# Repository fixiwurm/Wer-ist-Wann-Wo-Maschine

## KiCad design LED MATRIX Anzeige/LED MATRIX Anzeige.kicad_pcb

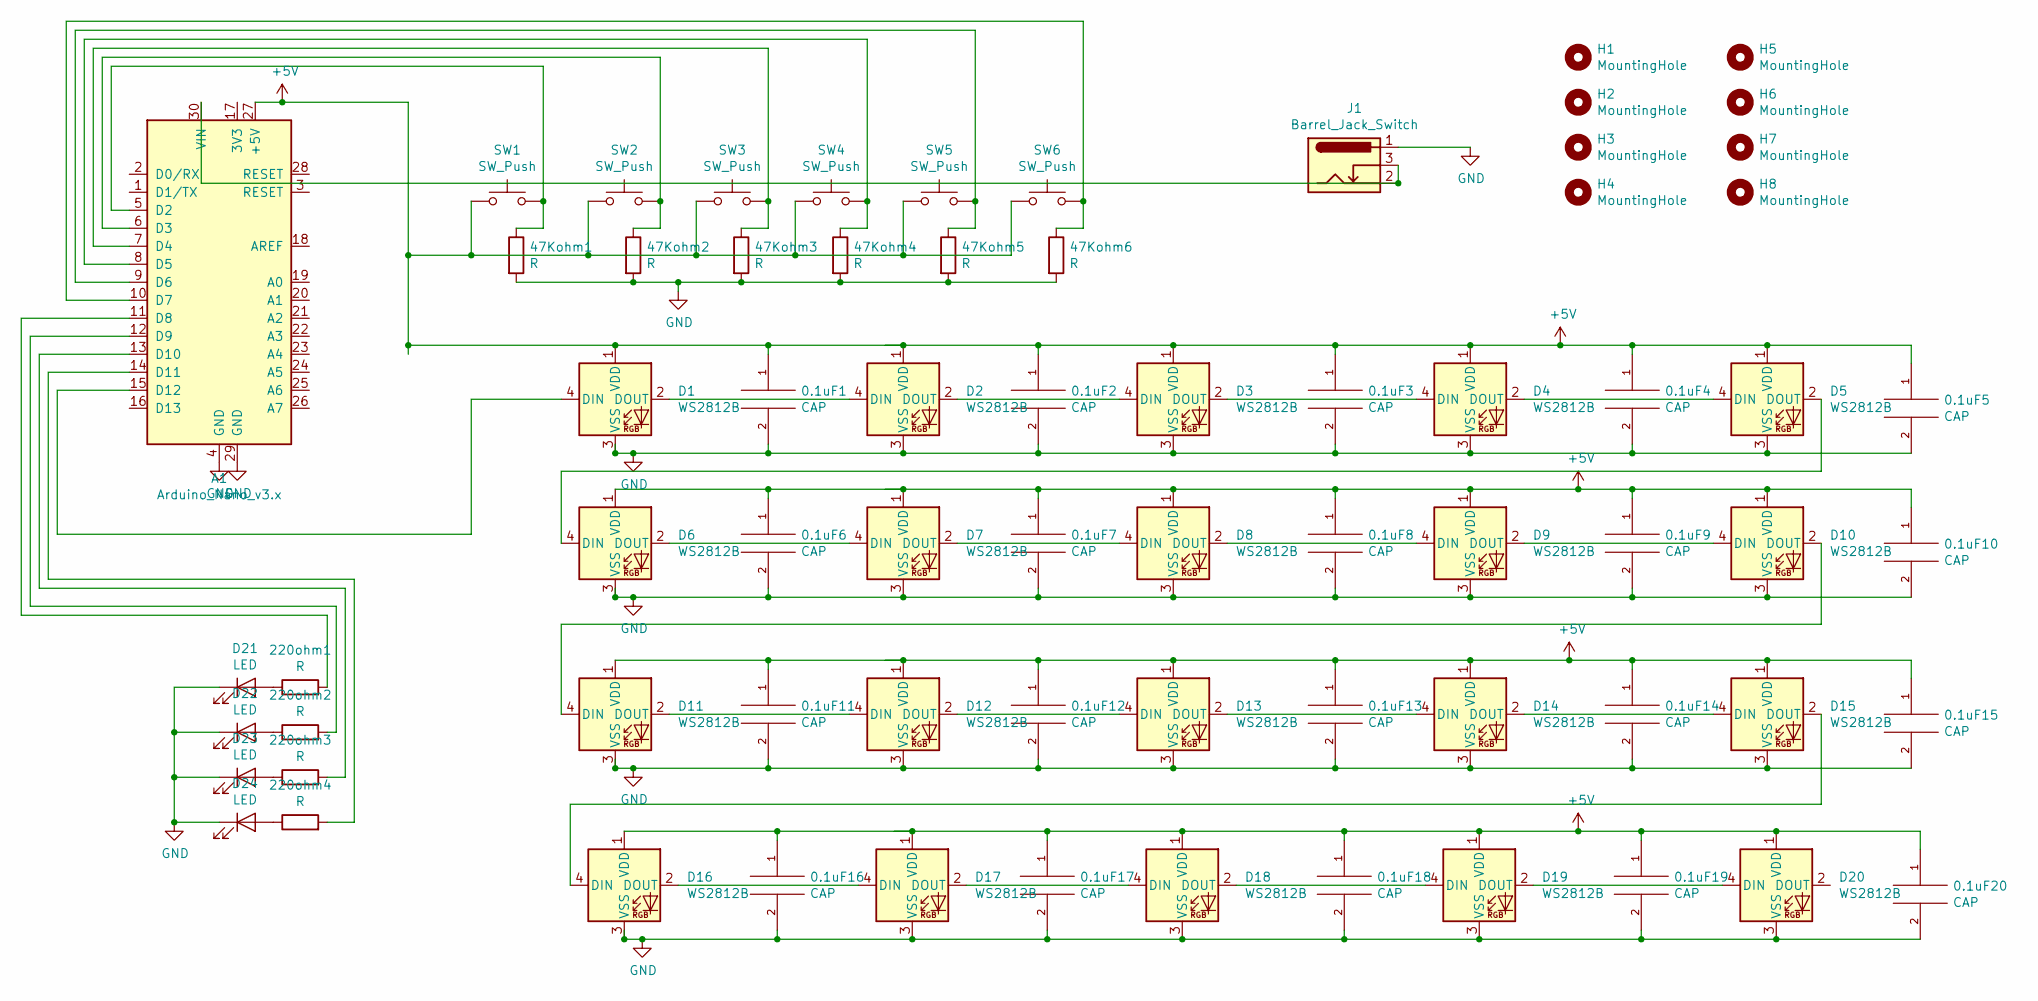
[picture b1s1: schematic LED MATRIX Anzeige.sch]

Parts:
0.1uF1, 0.1uF2, 0.1uF3, 0.1uF4, 0.1uF5, 0.1uF6, 0.1uF7, 0.1uF8, 0.1uF9, 0.1uF10, 0.1uF11, 0.1uF12, 0.1uF13, 0.1uF14, 0.1uF15, 0.1uF16, 0.1uF17, 0.1uF18, 0.1uF19, 0.1uF20: CAP; C_1206_3216Metric
47Kohm1, 47Kohm2, 47Kohm3, 47Kohm4, 47Kohm5, 47Kohm6, 220ohm1, 220ohm2, 220ohm3, 220ohm4: R; R_Axial_DIN0207_L6.3mm_D2.5mm_P10.16mm_Horizontal
A1: Arduino_Nano_v3.x; Arduino_Nano
D1, D2, D3, D4, D5, D6, D7, D8, D9, D10, D11, D12, D13, D14, D15, D16, D17, D18, D19, D20: WS2812B; LED_WS2812B_PLCC4_5.0x5.0mm_P3.2mm
D21, D22, D23, D24: LED; LED_D5.0mm
H1, H2, H3, H4: MountingHole; MountingHole_3.2mm_M3
H5, H6, H7, H8: MountingHole; MountingHole_5mm
J1: Barrel_Jack_Switch; BarrelJack_Horizontal
SW1, SW2, SW3, SW4, SW5, SW6: SW_Push; SW_PUSH_6mm

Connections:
+5V: 0.1uF1.1, 0.1uF2.1, 0.1uF3.1, 0.1uF4.1, 0.1uF5.1, 0.1uF6.1, 0.1uF7.1, 0.1uF8.1, 0.1uF9.1, 0.1uF10.1, 0.1uF11.1, 0.1uF12.1, 0.1uF13.1, 0.1uF14.1, 0.1uF15.1, 0.1uF16.1, 0.1uF17.1, 0.1uF18.1, 0.1uF19.1, 0.1uF20.1, A1.27 (+5V), D1.1 (VDD), D2.1 (VDD), D3.1 (VDD), D4.1 (VDD), D5.1 (VDD), D6.1 (VDD), D7.1 (VDD), D8.1 (VDD), D9.1 (VDD), D10.1 (VDD), D11.1 (VDD), D12.1 (VDD), D13.1 (VDD), D14.1 (VDD), D15.1 (VDD), D16.1 (VDD), D17.1 (VDD), D18.1 (VDD), D19.1 (VDD), D20.1 (VDD), SW1.1, SW2.1, SW3.1, SW4.1, SW5.1, SW6.1
GND: 0.1uF1.2, 0.1uF2.2, 0.1uF3.2, 0.1uF4.2, 0.1uF5.2, 0.1uF6.2, 0.1uF7.2, 0.1uF8.2, 0.1uF9.2, 0.1uF10.2, 0.1uF11.2, 0.1uF12.2, 0.1uF13.2, 0.1uF14.2, 0.1uF15.2, 0.1uF16.2, 0.1uF17.2, 0.1uF18.2, 0.1uF19.2, 0.1uF20.2, 47Kohm1.2, 47Kohm2.2, 47Kohm3.2, 47Kohm4.2, 47Kohm5.2, 47Kohm6.2, A1.4 (GND), A1.29 (GND), D1.3 (VSS), D2.3 (VSS), D3.3 (VSS), D4.3 (VSS), D5.3 (VSS), D6.3 (VSS), D7.3 (VSS), D8.3 (VSS), D9.3 (VSS), D10.3 (VSS), D11.3 (VSS), D12.3 (VSS), D13.3 (VSS), D14.3 (VSS), D15.3 (VSS), D16.3 (VSS), D17.3 (VSS), D18.3 (VSS), D19.3 (VSS), D20.3 (VSS), D21.1 (K), D22.1 (K), D23.1 (K), D24.1 (K), J1.1
unnamed: 47Kohm1.1, A1.5 (D2), SW1.2
unnamed: 47Kohm2.1, A1.6 (D3), SW2.2
unnamed: 47Kohm3.1, A1.7 (D4), SW3.2
unnamed: 47Kohm4.1, A1.8 (D5), SW4.2
unnamed: 47Kohm5.1, A1.9 (D6), SW5.2
unnamed: 47Kohm6.1, A1.10 (D7), SW6.2
unnamed: 220ohm1.1, D21.2 (A)
unnamed: 220ohm1.2, A1.11 (D8)
unnamed: 220ohm2.1, D22.2 (A)
unnamed: 220ohm2.2, A1.12 (D9)
unnamed: 220ohm3.1, D23.2 (A)
unnamed: 220ohm3.2, A1.13 (D10)
unnamed: 220ohm4.1, D24.2 (A)
unnamed: 220ohm4.2, A1.14 (D11)
unnamed: A1.15 (D12), D1.4 (DIN)
unnamed: A1.30 (VIN), J1.2, J1.3
unnamed: D1.2 (DOUT), D2.4 (DIN)
unnamed: D2.2 (DOUT), D3.4 (DIN)
unnamed: D3.2 (DOUT), D4.4 (DIN)
unnamed: D4.2 (DOUT), D5.4 (DIN)
unnamed: D5.2 (DOUT), D6.4 (DIN)
unnamed: D6.2 (DOUT), D7.4 (DIN)
unnamed: D7.2 (DOUT), D8.4 (DIN)
unnamed: D8.2 (DOUT), D9.4 (DIN)
unnamed: D10.2 (DOUT), D11.4 (DIN)
unnamed: D9.2 (DOUT), D10.4 (DIN)
unnamed: D11.2 (DOUT), D12.4 (DIN)
unnamed: D12.2 (DOUT), D13.4 (DIN)
unnamed: D13.2 (DOUT), D14.4 (DIN)
unnamed: D14.2 (DOUT), D15.4 (DIN)
unnamed: D15.2 (DOUT), D16.4 (DIN)
unnamed: D16.2 (DOUT), D17.4 (DIN)
unnamed: D17.2 (DOUT), D18.4 (DIN)
unnamed: D18.2 (DOUT), D19.4 (DIN)
unnamed: D19.2 (DOUT), D20.4 (DIN)

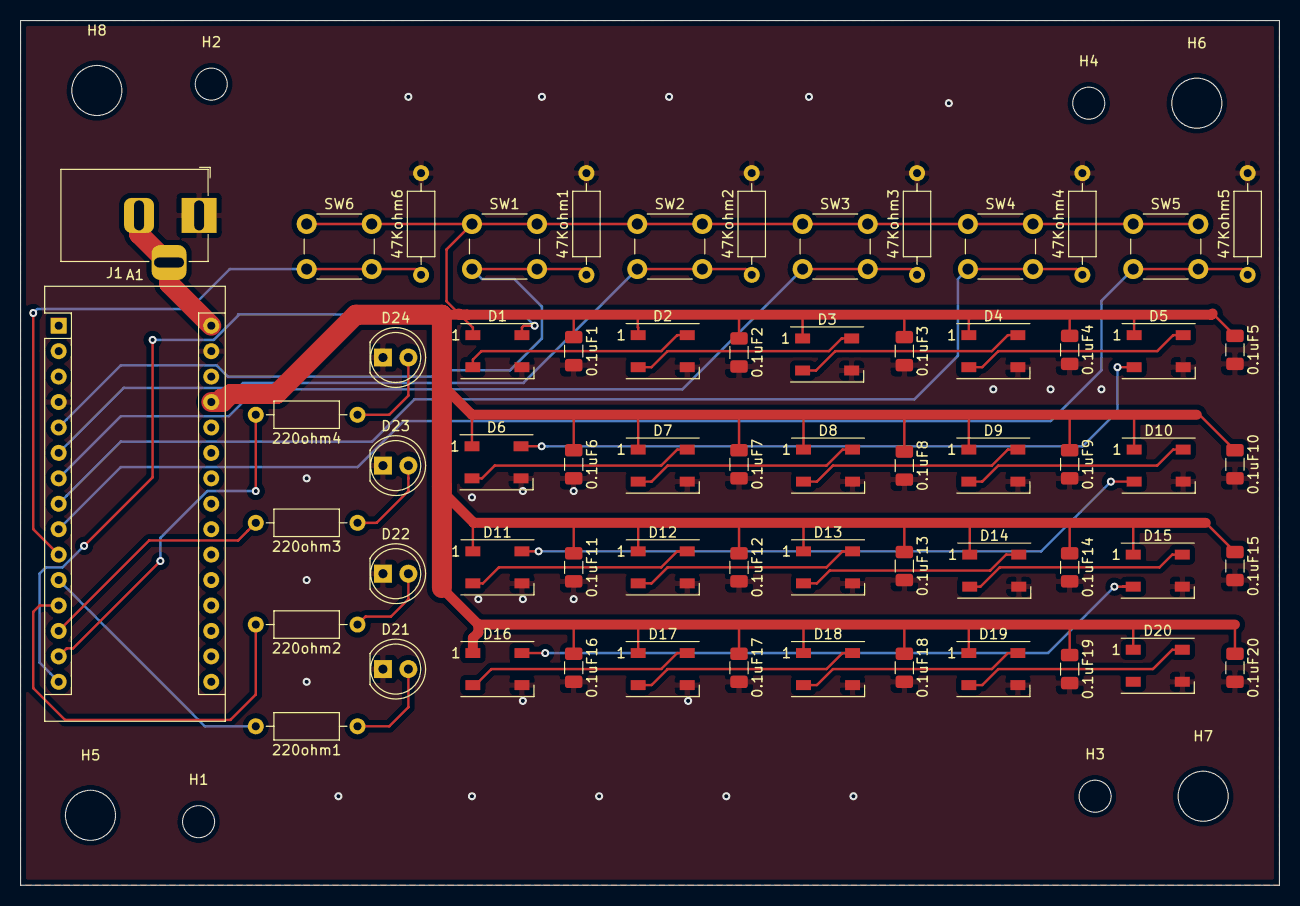
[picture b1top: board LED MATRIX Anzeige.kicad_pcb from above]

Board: 2 copper layers, 125.7 x 86.4 mm, 70 parts (0 on the bottom side), 37 nets.
